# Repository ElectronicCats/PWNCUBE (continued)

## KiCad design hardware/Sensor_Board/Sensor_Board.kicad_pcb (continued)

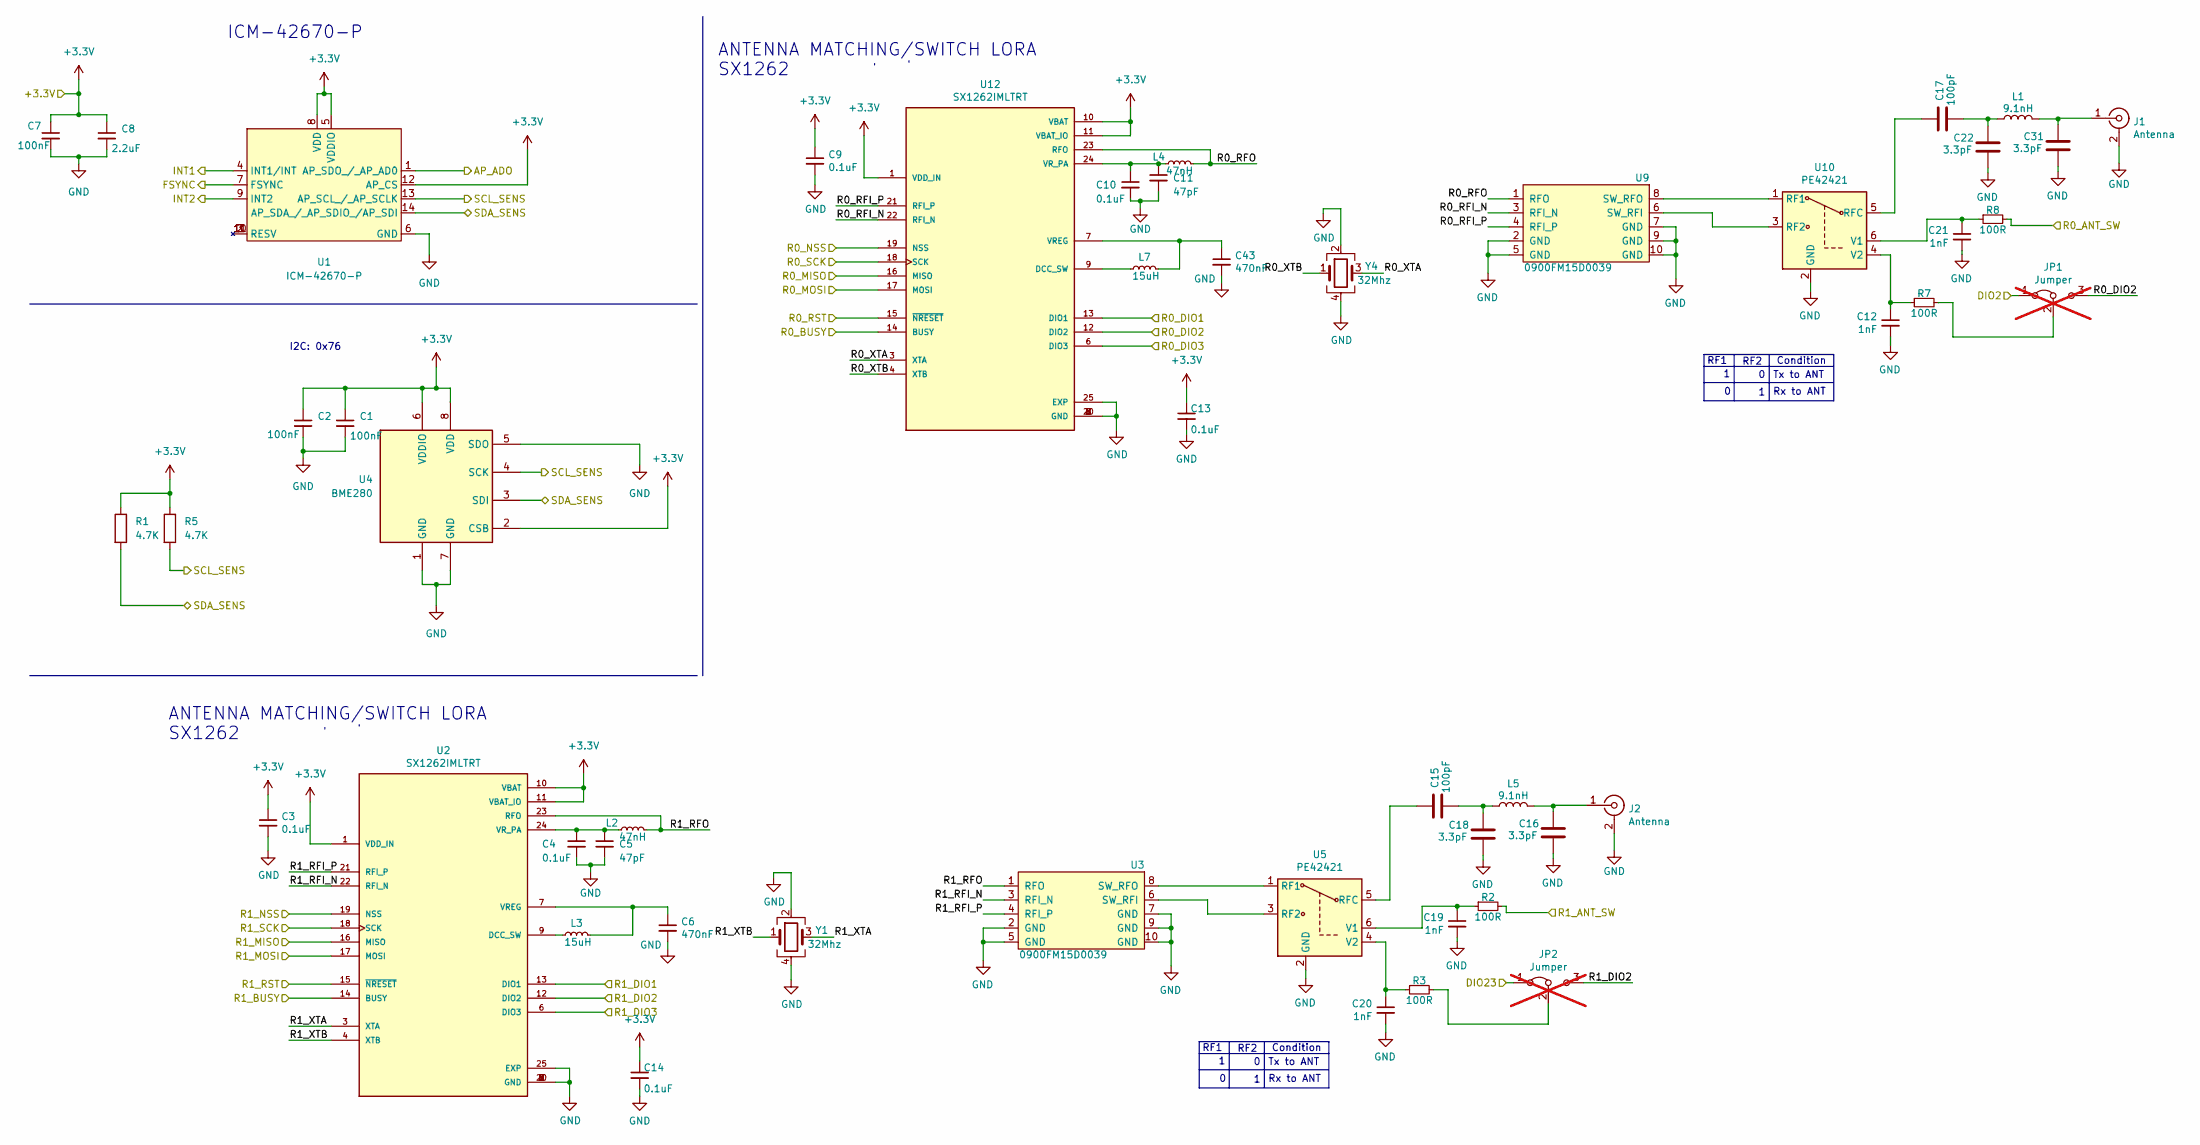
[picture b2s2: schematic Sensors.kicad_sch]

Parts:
C1, C2, C7: 100nF; C_0402_1005Metric; LCSC# C56392
C3, C4, C9, C10, C13, C14: 0.1uF; C_0402_1005Metric; LCSC# C56392
C5, C11: 47pF; C_0402_1005Metric; LCSC# C437519
C6, C43: 470nF; C_0402_1005Metric; LCSC# C47339
C8: 2.2uF; C_0402_1005Metric
C12, C19, C20, C21: 1nF; C_0402_1005Metric; LCSC# C710873
C15, C17: 100pF; C_0402_1005Metric; LCSC# C541374
C16, C18, C22, C31: 3.3pF; C_0402_1005Metric; LCSC# C1565
J1, J2: Antenna; SMA_EDGE; LCSC# C530661
JP1, JP2: Jumper; SolderJumper-3_P1.3mm_Bridged12_RoundedPad1.0x1.5mm_NumberL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; LCSC# ---; not fitted
L1, L5: 9.1nH; L_0603_1608Metric; LCSC# C395094
L2, L4: 47nH; L_0603_1608Metric; LCSC# C578001
L3, L7: 15uH; L_0603_1608Metric; LCSC# C57838
R1, R5: 4.7K; R_0402_1005Metric_Pad0.72x0.64mm_HandSolder; LCSC# C400631
R2, R3, R7, R8: 100R; R_0402_1005Metric; LCSC# C25076
U1: ICM-42670-P; LGA-14_3x2.5mm_P0.5mm_LayoutBorder3x4y; LCSC# C3288646
U2, U12: SX1262IMLTRT; QFN-24-1EP_4x4mm_P0.5mm_EP2.65x2.65mm; Mouser# 947-SX1262IMLTRT
U3, U9: 0900FM15D0039; 0900FM15D0039E; Mouser# 609-0900FM15D0039E
U4: BME280; Bosch_LGA-8_2.5x2.5mm_P0.65mm_ClockwisePinNumbering; LCSC# C92489
U5, U10: PE42421; SOT-363_SC-70-6; Mouser# 81-PE42421SCAA-Z; LCSC# C470893
Y1, Y4: 32Mhz; Crystal_SMD_2520-4Pin_2.5x2.0mm; LCSC# C255969

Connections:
+3.3V: C1.1, C2.1, C3.1, C7.1, C8.1, C9.1, C13.1, C14.1, R1.1, R5.1, U1.5 (VDDIO), U1.8 (VDD), U1.12 (AP_CS), U2.1 (VDD_IN), U2.10 (VBAT), U2.11 (VBAT_IO), U4.2 (CSB), U4.6 (VDDIO), U4.8 (VDD), U12.1 (VDD_IN), U12.10 (VBAT), U12.11 (VBAT_IO); also elsewhere on the board
/Inputs_Connectors/AP_ADO: U1.1 (AP_SDO_/_AP_AD0); also elsewhere on the board
/Inputs_Connectors/DIO2: JP1.1 (A); also elsewhere on the board
/Inputs_Connectors/DIO23: JP2.1 (A); also elsewhere on the board
/Inputs_Connectors/FSYNC: U1.7 (FSYNC); also elsewhere on the board
/Inputs_Connectors/INT1: U1.4 (INT1/INT); also elsewhere on the board
/Inputs_Connectors/INT2: U1.9 (INT2); also elsewhere on the board
/Inputs_Connectors/R0_ANT_SW: R8.2; also elsewhere on the board
/Inputs_Connectors/R0_BUSY: U12.14 (BUSY); also elsewhere on the board
/Inputs_Connectors/R0_DIO1: U12.13 (DIO1); also elsewhere on the board
/Inputs_Connectors/R0_DIO3: U12.6 (DIO3); also elsewhere on the board
/Inputs_Connectors/R0_MISO: U12.16 (MISO); also elsewhere on the board
/Inputs_Connectors/R0_MOSI: U12.17 (MOSI); also elsewhere on the board
/Inputs_Connectors/R0_NSS: U12.19 (NSS); also elsewhere on the board
/Inputs_Connectors/R0_RST: U12.15 (~NRESET); also elsewhere on the board
/Inputs_Connectors/R0_SCK: U12.18 (SCK); also elsewhere on the board
/Inputs_Connectors/R1_ANT_SW: R2.2; also elsewhere on the board
/Inputs_Connectors/R1_BUSY: U2.14 (BUSY); also elsewhere on the board
/Inputs_Connectors/R1_DIO1: U2.13 (DIO1); also elsewhere on the board
/Inputs_Connectors/R1_DIO3: U2.6 (DIO3); also elsewhere on the board
/Inputs_Connectors/R1_MISO: U2.16 (MISO); also elsewhere on the board
/Inputs_Connectors/R1_MOSI: U2.17 (MOSI); also elsewhere on the board
/Inputs_Connectors/R1_NSS: U2.19 (NSS); also elsewhere on the board
/Inputs_Connectors/R1_RST: U2.15 (~NRESET); also elsewhere on the board
/Inputs_Connectors/R1_SCK: U2.18 (SCK); also elsewhere on the board
/Inputs_Connectors/SCL_SENS: R5.2, U1.13 (AP_SCL_/_AP_SCLK), U4.4 (SCK); also elsewhere on the board
/Inputs_Connectors/SDA_SENS: R1.2, U1.14 (AP_SDA_/_AP_SDIO_/AP_SDI), U4.3 (SDI); also elsewhere on the board
/Sensors/R0_DIO2: JP1.3 (B), U12.12 (DIO2); also elsewhere on the board
/Sensors/R0_RFI_N: U9.3 (RFI_N), U12.22 (RFI_N)
/Sensors/R0_RFI_P: U9.4 (RFI_P), U12.21 (RFI_P)
/Sensors/R0_RFO: L4.2, U9.1 (RFO), U12.23 (RFO)
/Sensors/R0_XTA: U12.3 (XTA), Y4.3
/Sensors/R0_XTB: U12.4 (XTB), Y4.1
/Sensors/R1_DIO2: JP2.3 (B), U2.12 (DIO2); also elsewhere on the board
/Sensors/R1_RFI_N: U2.22 (RFI_N), U3.3 (RFI_N)
/Sensors/R1_RFI_P: U2.21 (RFI_P), U3.4 (RFI_P)
/Sensors/R1_RFO: L2.2, U2.23 (RFO), U3.1 (RFO)
/Sensors/R1_XTA: U2.3 (XTA), Y1.3
/Sensors/R1_XTB: U2.4 (XTB), Y1.1
GND: C1.2, C2.2, C3.2, C4.2, C5.2, C6.2, C7.2, C8.2, C9.2, C10.2, C11.2, C12.2, C13.2, C14.2, C16.2, C18.2, C19.2, C20.2, C21.2, C22.2, C31.2, C43.2, J1.2 (Ext), J2.2 (Ext), U1.6 (GND), U2.2 (GND), U2.5 (GND), U2.8 (GND), U2.20 (GND), U2.25 (EXP), U3.2 (GND), U3.5 (GND), U3.7 (GND), U3.9 (GND), U3.10 (GND), U4.1 (GND), U4.5 (SDO), U4.7 (GND), U5.2 (GND), U9.2 (GND), U9.5 (GND), U9.7 (GND), U9.9 (GND), U9.10 (GND), U10.2 (GND), U12.2 (GND), U12.5 (GND), U12.8 (GND), U12.20 (GND), U12.25 (EXP), Y1.2, Y1.4, Y4.2, Y4.4; also elsewhere on the board
unnamed: C15.2, C18.1, L5.2
unnamed: C17.2, C22.1, L1.2
unnamed: C31.1, J1.1 (In), L1.1
unnamed: C16.1, J2.1 (In), L5.1
unnamed: JP1.2 (C), R7.2
unnamed: JP2.2 (C), R3.2
unnamed: L3.1, U2.9 (DCC_SW)
unnamed: C6.1, L3.2, U2.7 (VREG)
unnamed: C4.1, C5.1, L2.1, U2.24 (VR_PA)
unnamed: U3.6 (SW_RFI), U5.3 (RF2)
unnamed: U3.8 (SW_RFO), U5.1 (RF1)
unnamed: C15.1, U5.5 (RFC)
unnamed: C19.1, R2.1, U5.6 (V1)
unnamed: C20.1, R3.1, U5.4 (V2)
unnamed: U9.8 (SW_RFO), U10.1 (RF1)
unnamed: U9.6 (SW_RFI), U10.3 (RF2)
unnamed: C17.1, U10.5 (RFC)
unnamed: C21.1, R8.1, U10.6 (V1)
unnamed: C12.1, R7.1, U10.4 (V2)
unnamed: L7.1, U12.9 (DCC_SW)
unnamed: C43.1, L7.2, U12.7 (VREG)
unnamed: C10.1, C11.1, L4.1, U12.24 (VR_PA)

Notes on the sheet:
ANTENNA MATCHING/SWITCH LORA
Condition
Tx to ANT
SX1262
RF2
RF1
Rx to ANT
I2C: 0x76
ICM-42670-P

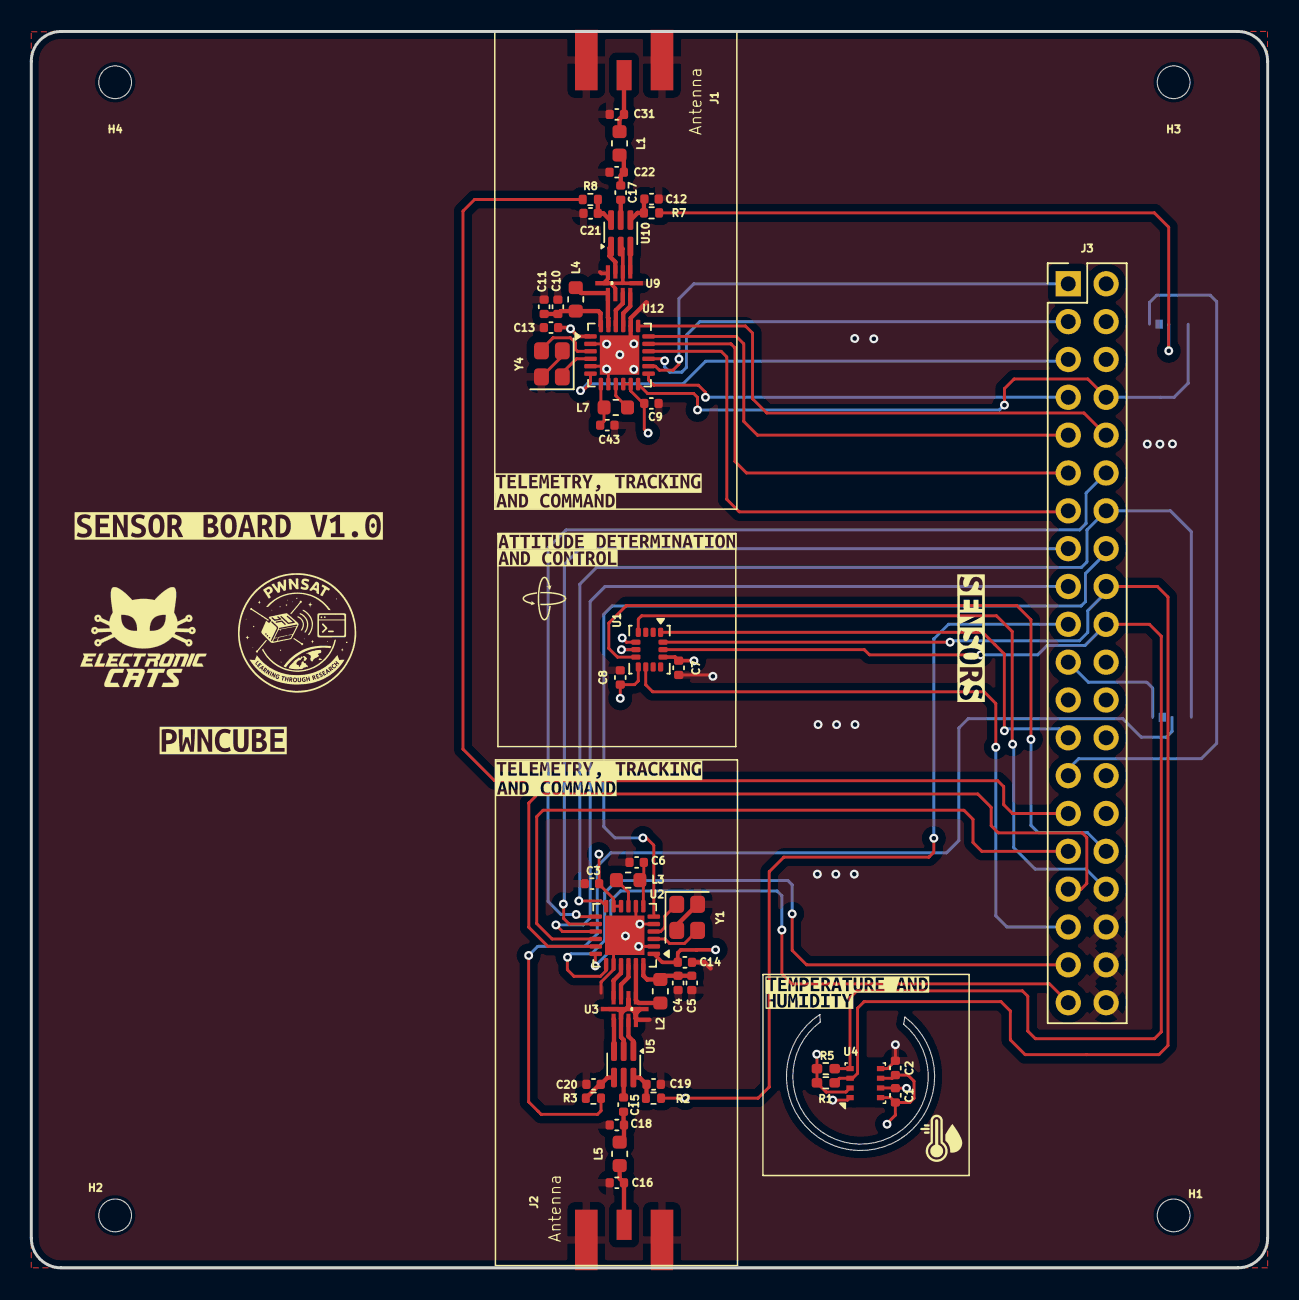
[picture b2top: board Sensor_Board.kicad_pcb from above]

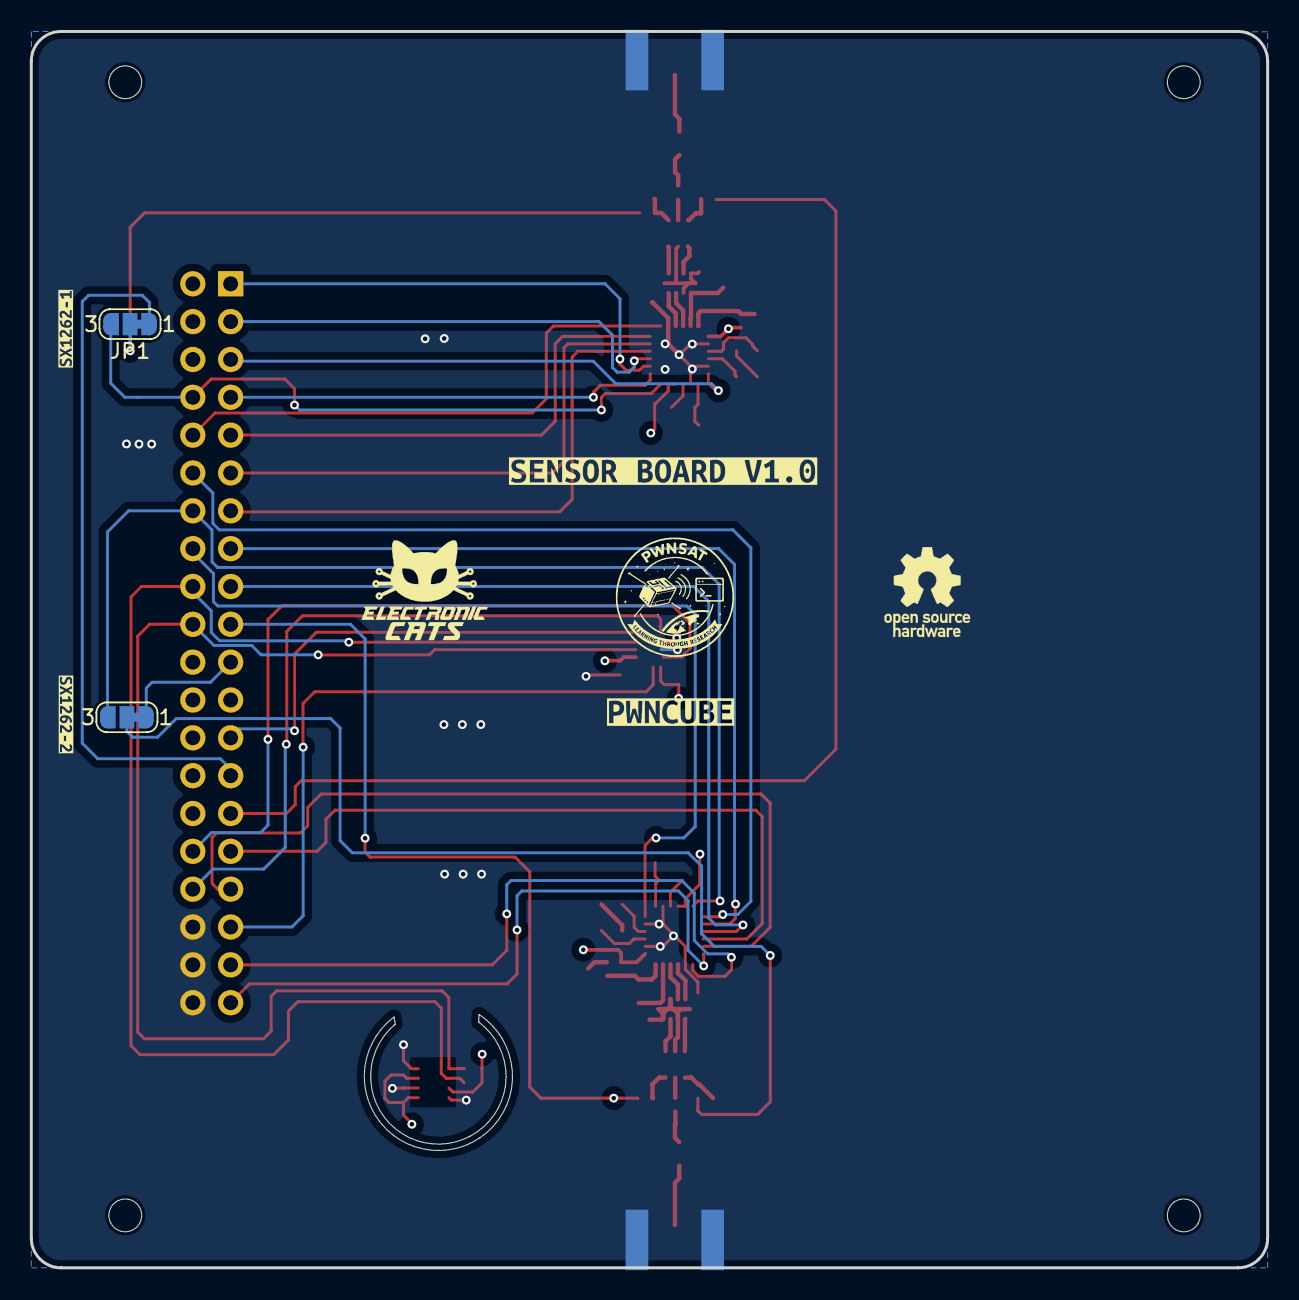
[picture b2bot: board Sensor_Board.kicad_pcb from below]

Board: 4 copper layers, 83.0 x 83.0 mm, 70 parts (6 on the bottom side), 62 nets.

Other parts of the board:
H1, H2, H3, H4: MountingHole; MountingHole_2.2mm_M2
kibuzzard-69860F52: G***; kibuzzard-69860F52
kibuzzard-69860F65: G***; kibuzzard-69860F65
kibuzzard-69866AEC: G***; kibuzzard-69866AEC
kibuzzard-69866B09: G***; kibuzzard-69866B09
kibuzzard-698518BF, kibuzzard-698518BF#2: G***; kibuzzard-698518BF
kibuzzard-698518EC, kibuzzard-698518EC#2: G***; kibuzzard-698518EC
kibuzzard-698668F8: G***; kibuzzard-698668F8
kibuzzard-698669D4, kibuzzard-698669D4#2: G***; kibuzzard-698669D4
kibuzzard-698669E3, kibuzzard-698669E3#2: G***; kibuzzard-698669E3
kibuzzard-6985197E: G***; kibuzzard-6985197E
kibuzzard-69866904: G***; kibuzzard-69866904

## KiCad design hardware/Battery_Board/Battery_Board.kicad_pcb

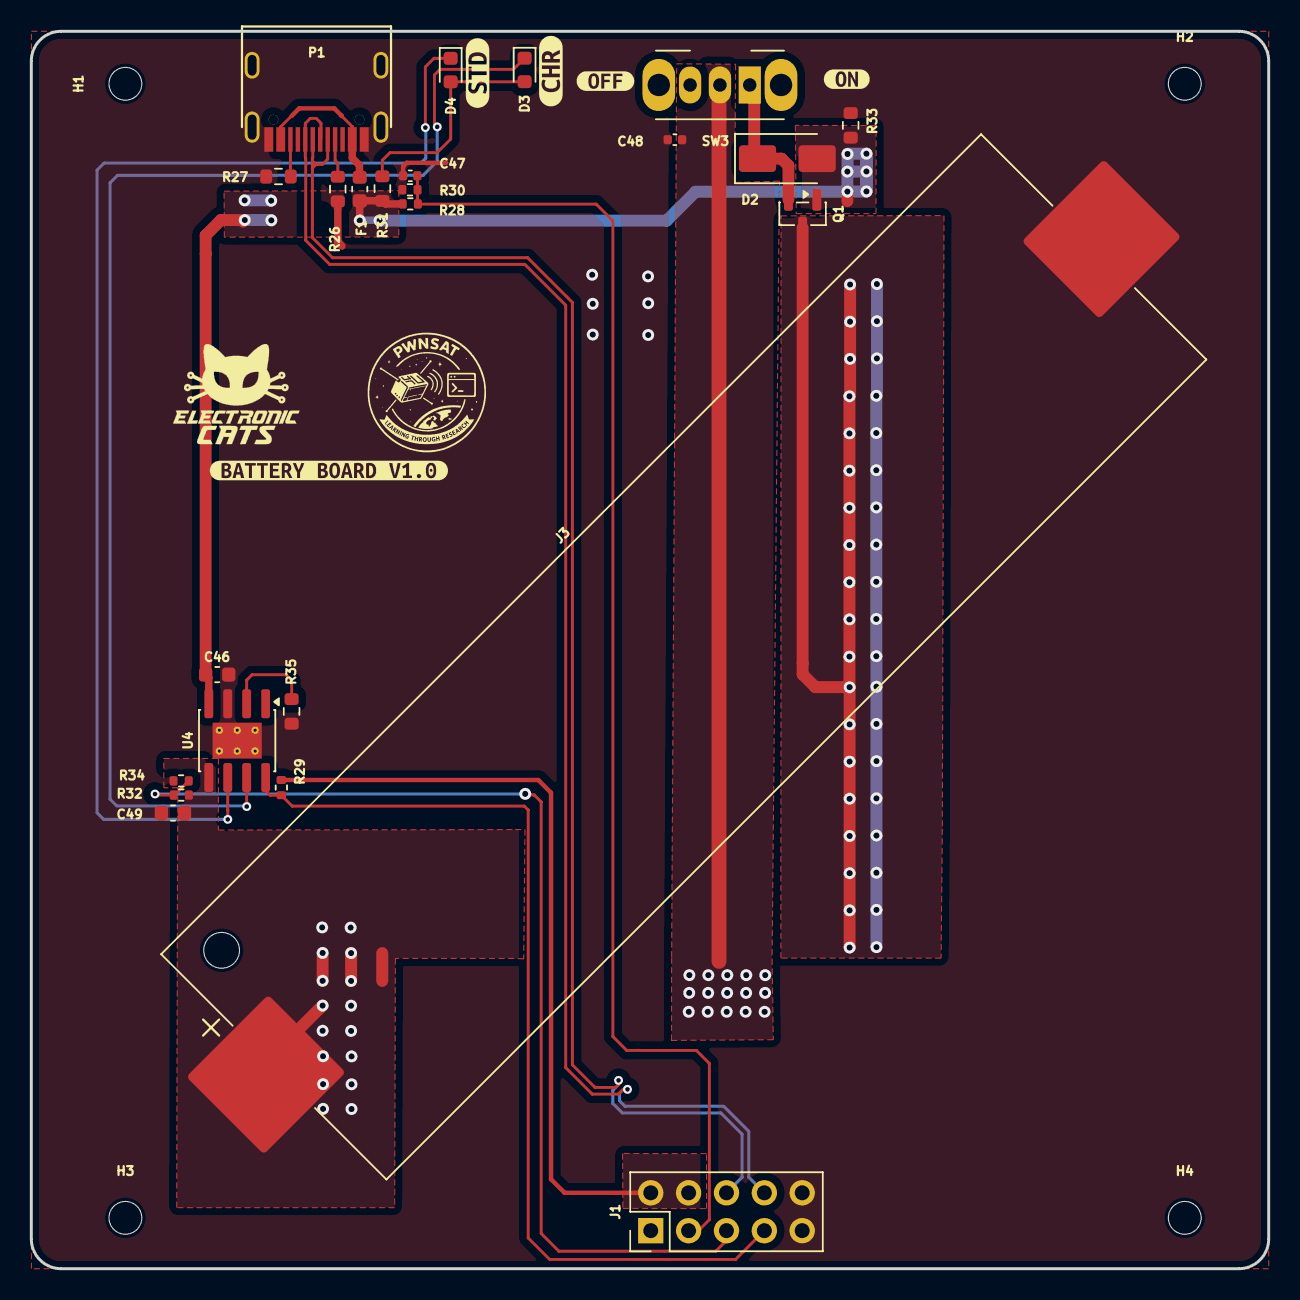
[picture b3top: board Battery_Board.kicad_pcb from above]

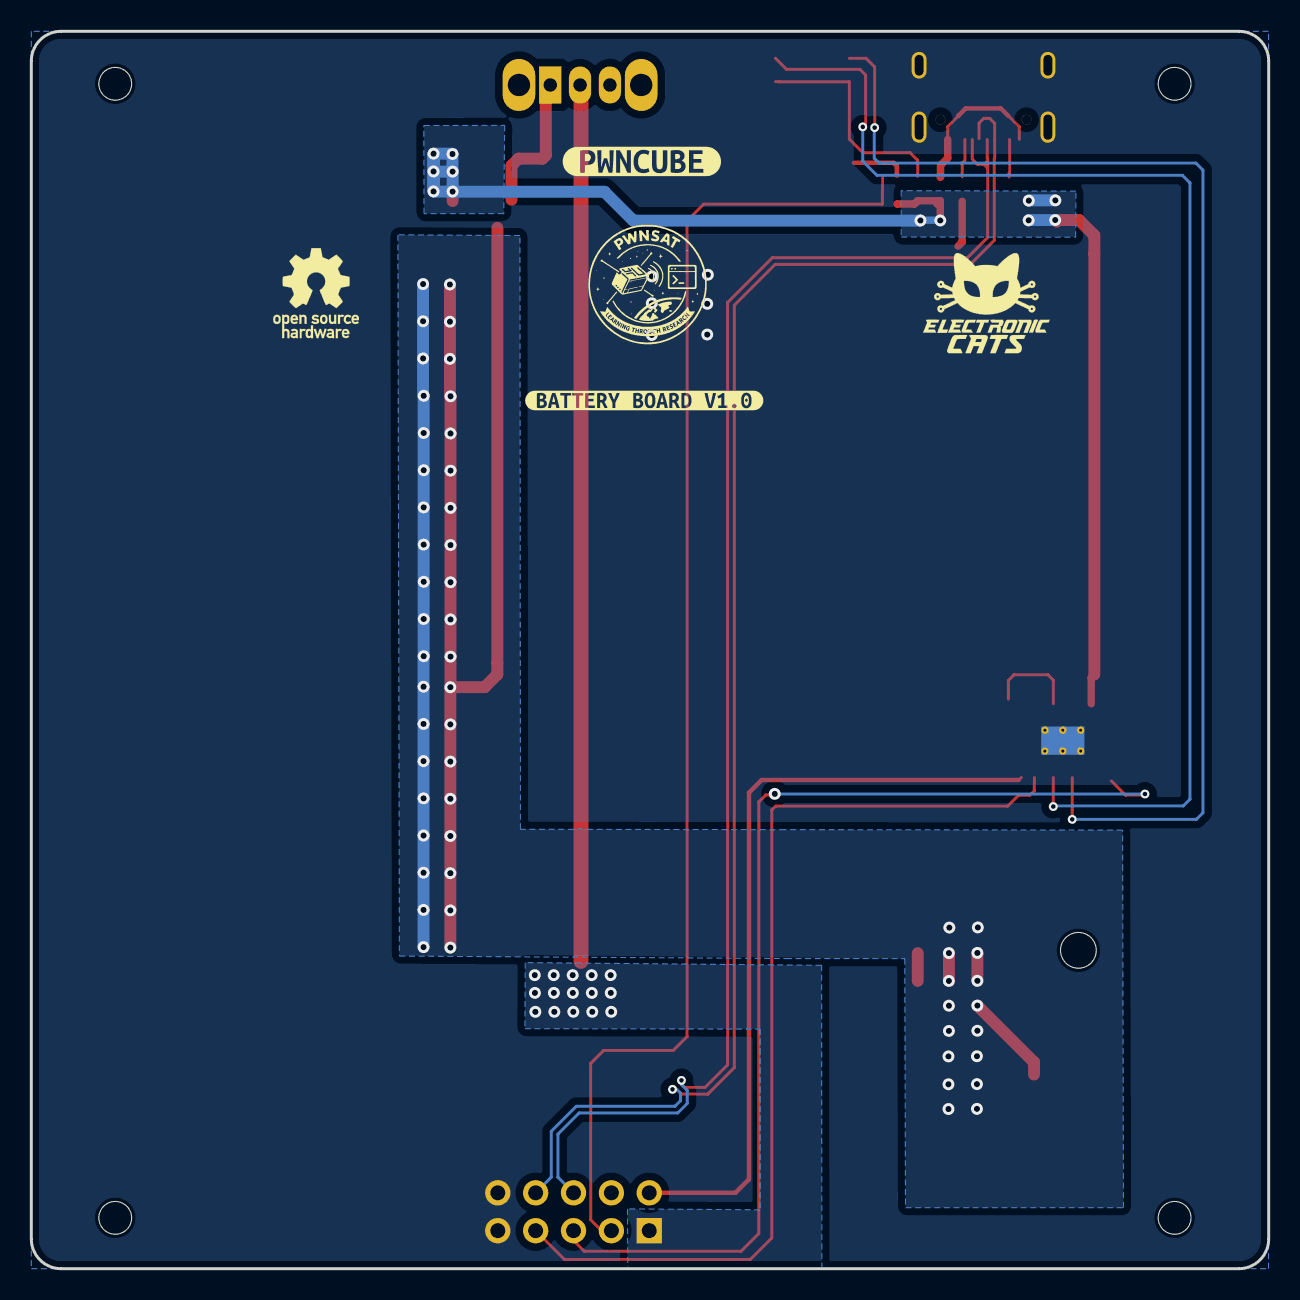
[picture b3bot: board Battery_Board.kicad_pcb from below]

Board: 2 copper layers, 83.0 x 83.0 mm, 35 parts (2 on the bottom side), 18 nets.

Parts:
C46, C49: 10uF; C_0603_1608Metric
C47: 100nF; C_0402_1005Metric
C48: 10uF; C_0402_1005Metric
D2: SS34; D_SMA
D3, D4: LED; LED_0603_1608Metric
F1: 2A; Fuse_0603_1608Metric
H1, H2, H3, H4: MountingHole; MountingHole_2.2mm_M2
J1: Source; PinHeader_2x05_P2.54mm_Vertical
J3: Battery; BatteryHolder_Keystone_1042_1x18650
P1: USB_C_Plug_USB2.0; C393939
Q1: DMG3415U-7; SOT-23
R26, R27: 5k1; R_0603_1608Metric
R28, R29, R34: 10K; R_0402_1005Metric
R30: 18k; R_0402_1005Metric
R31, R35: 2K; R_0603_1608Metric
R32: 10.7K; R_0402_1005Metric
R33: 100K; R_0603_1608Metric
SW3: ON; SW_Slide_SPDT_Angled_CK_OS102011MA1Q
U4: TP4056; SOIC-8-1EP_3.9x4.9mm_P1.27mm_EP2.41x3.3mm_ThermalVias
kibuzzard-698511AF: G***; kibuzzard-698511AF
kibuzzard-698511C2: G***; kibuzzard-698511C2
kibuzzard-6985125C: G***; kibuzzard-6985125C
kibuzzard-69851248, kibuzzard-69851248#2: G***; kibuzzard-69851248
kibuzzard-69851454: G***; kibuzzard-69851454
kibuzzard-69851473: G***; kibuzzard-69851473

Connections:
+3.3V: J1.2, J1.4, R29.1
+BATT: C49.1, J3.1, Q1.3 (D), R32.1, U4.5 (BAT)
/Batt_Connector/2_DN: J1.6, P1.A7 (D-)
/Batt_Connector/2_DP: J1.8, P1.A6 (D+)
/Batt_Connector/Battery: J1.5, R32.2, R34.1
/Batt_Connector/Enable: J1.7, R29.2, U4.8 (CE)
/Batt_Connector/USB_DET: C47.1, J1.3, R28.1, R30.1
GND: C46.1, C47.2, C48.2, C49.2, J1.9, J1.10, J3.2, P1.A1 (GND), P1.S1 (SHIELD), R26.1, R27.1, R30.2, R33.2, R34.2, R35.2, U4.3 (GND), U4.9 (EPAD)
unnamed: D2.1 (K), Q1.2 (S), SW3.1 (A)
unnamed: D3.2 (A), D4.2 (A), R31.2
unnamed: D3.1 (K), U4.7 (~CHRG)
unnamed: D4.1 (K), U4.6 (~STDBY)
unnamed: F1.1, P1.A4 (VBUS)
unnamed: P1.A5 (CC), R26.2
unnamed: P1.B5 (VCONN), R27.2
unnamed: R35.1, U4.2 (PROG)
VBUS: C46.2, D2.2 (A), F1.2, Q1.1 (G), R28.2, R31.1, R33.1, U4.4 (V_{CC})
VCC: C48.1, J1.1, SW3.2 (B)

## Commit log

2026-01-12 feat(Hw): Started_sch
2026-01-13 Feat(hw):Added_LoRa_module
2026-01-13 feat(Hw): Added_BOM
2026-01-15 feat(Hw):Sch_Updated
    Pending_Sensor_Connector
2026-01-19 feat(Hw):Init_Floorplan
2026-01-20 feat(Hw):Update_Floorplan_Init_First _route
    Pending_Battery_Type
2026-01-21 feat(Hw):Batt_Board_Pro_Added
2026-01-22 feat(Hw):Battery_Board_pro_Updated
2026-01-23 feat(Hw):Update_Battery_Sch_And_Sensors_And_PWNCube
    pending_Outputs_connectors
2026-01-26 feat(Hw):floorplans_updated
2026-01-27 feat(Hw):PCB_PwnSat_And_Battery_Updated
2026-01-28 feat(Hw):Route_Updating_PWNCube_Board
2026-02-03 feat(Hw):Route_UpdatedPWNcube_
    Pending_3v3
2026-02-04 feat(Hw):Update_Route_And_3d_Model_PWNsat_Batt_Board_And_Sensors
2026-02-04 feat(Hw):Boards_Updated
    Pending_Sensors_Board
2026-02-05 fix(Hw):Tracks_modified
2026-02-05 feat(Hw):Labels_Added
2026-02-06 feat(Hw):Update_Labels
2026-02-06 feat(Hw):BME280_Moved
2026-02-06 feat(Hw):labels_updated
2026-02-09 fix(Hw):Label_Main_Updated
2026-02-09 feat(Hw):BoM´s_Updated
2026-03-13 feat(Hw):Route_Updated
    Pending review
2026-03-13 feat(Hw):update_route
2026-03-17 Feat(Hw): Change to 4-layer
2026-03-30 Add CERN Open Hardware Licence v1.2
    Added CERN Open Hardware Licence v1.2 to the project.
2026-04-01 Updated for Arsenal USA
    Updated for Arsenal USA
